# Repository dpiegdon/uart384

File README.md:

<!-- vim: tw=72 fo+=a
-->

UART384 - FPGA devboard & USB-stick
===================================

<div>

</div>

<div>

</div>

This is a mini-devboard for the Lattice iCE40LP384, the *BEST* 🔍 FPGA
ever!

Features:
- USB-stick form-factor
- USB is connected to Silabs CP2102 USB-to-UART bridge
- Tiny Lattice iCE40LP384 with connections:
  - 384 LUTs/FFs
  - UART
  - 2 LEDs
  - 1 push-button
  - 8 GPIOs on pinheader
  - 32MHz oscillator
- small flash for bitstream
- TC2050 connector (bottom side) for programming the flash

NOTE: device is not programmable via USB

Gateware
========

"Why?", you ask?

Mostly for fun and training; there are a few gateware options available in this repository:

Entropy generator
-----------------

`gateware/entropy_generator.v`

High quality entropy source using metastability from ringoscillators fed
into the spongent hash algorithm. 

This is one of the original reasons this board was created for: I wanted
a USB stick that generates cryptographically sound entropy that can be
used to enhance system entropy on linux.

`gateware/tools/seedrng.py` can be used to receive the entropy and
inject it directly into the kernel entropy pool.

SPI and GPIO over UART tunnel
-----------------------------

`gateware/relay_spi.v`

This variant allows complex muxing of SPI lines from an SPI master core
to all GPIO1..8 pins, as well as the internal program flash. All these
pins can also be muxed as GPIO input or output and controlled/sampled.
All that via a simple UART protocol.

This gives full control of inputs and outputs, as well as efficient SPI
communication via SPI core, in any configuration. The SPI core is used
for SPI transfer by pulling RTS down, then CS is automatically pulled
down and data is seemlessly interchanged between SPI and UART.

This e.g. allows reprogramming the internal flash, or external SPI
devices, including Lattice iCE40 FPGAs if GPIOs are used to trigger
their CRESET. Since CDONE can also be sampled, this also allows
programming any iCE40 FPGA in slave mode, fully replacing any other
needed programming board to flash/program a Lattice iCE40 FPGA. Note
that the FPGA is pretty much full, no further features will be added to
this gateware.

See `gateware/tools/spi_device.py` for general SPI command abstraction,
and `gateware/tools/flashtool.py` and `gateware/tools/spi_device.py` as
an example client to work with the onboard (or any other) serial flash.

Ring oscillator entropy generator
---------------------------------

`gateware/ring_noise.v`

Low quality entropy generator using metastability from ringoscillators
fed into a linear feedback shift register.

UART pass-through
-----------------

`gateware/uart_passthrough.v`

A simple example that only passes UART signals along to the GPIO header
and shows changes on RX/TX lines on the LEDs (with some timeout).

Variable delay ring oscillator
------------------------------

`gateware/variable_ringoscillator.v`

Experiments with a ringoscillator with a reconfigurable delay-line.
Delay can be changed at runtime via UART.

License
=======

The hardware (Schematic, PCB) is licensed under CERN-OHL-W v2.
See `cern_ohl_w_v2.txt`.

The software is licensed under LGPL v2.0, unless specified otherwise
in a subrepository. See `LGPLv2.0.txt`.

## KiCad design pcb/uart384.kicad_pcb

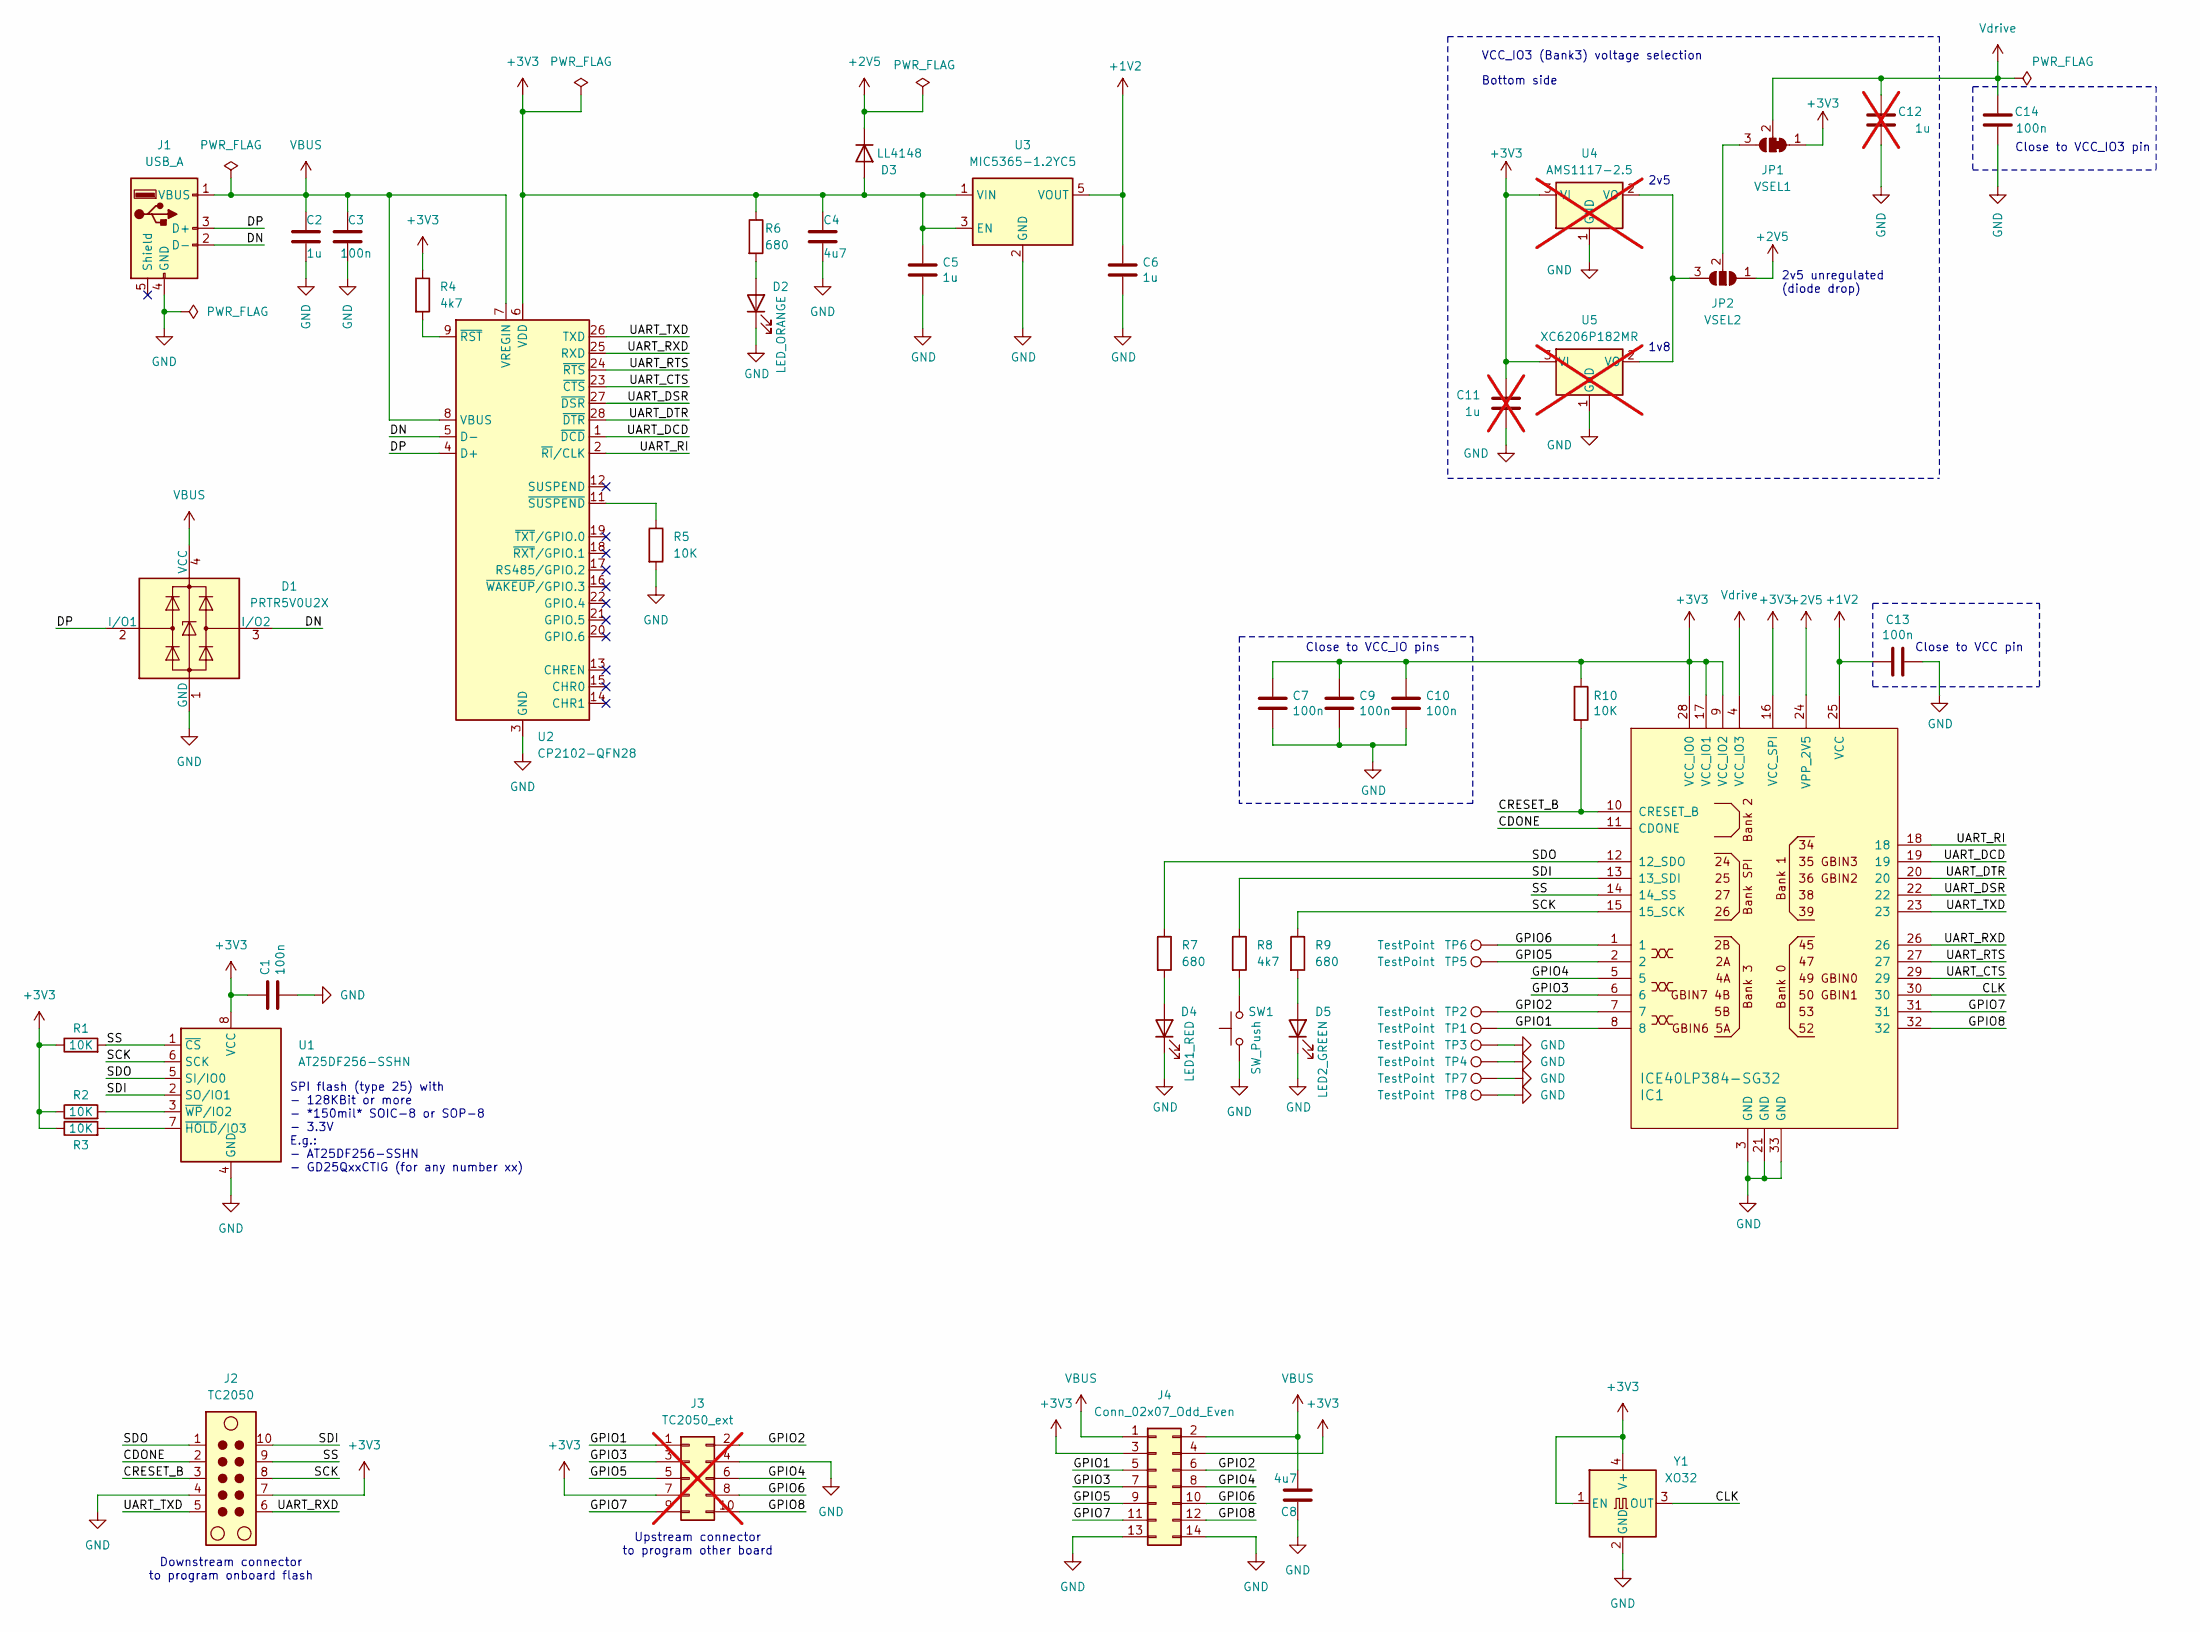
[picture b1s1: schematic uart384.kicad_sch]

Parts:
C1, C3, C7, C9, C10, C13, C14: 100n; C_0603_1608Metric
C2, C5, C6: 1u; C_0603_1608Metric
C4, C8: 4u7; C_0603_1608Metric
C11, C12: 1u; C_0603_1608Metric; not fitted
D1: PRTR5V0U2X; SOT-143
D2: LED_ORANGE; LED_0603_1608Metric
D3: LL4148; D_MiniMELF
D4: LED1_RED; LED_0603_1608Metric
D5: LED2_GREEN; LED_0603_1608Metric
IC1: ICE40LP384-SG32; QFN-32-1EP_5x5mm_P0.5mm_EP3.6x3.6mm
J1: USB_A; CONN-USB-A-PCB-TRACES
J2: TC2050; Tag-Connect_TC2050-IDC-NL_2x05_P1.27mm_Vertical
J3: TC2050_ext; PinHeader_2x05_P2.54mm_Vertical_SMD; not fitted
J4: Conn_02x07_Odd_Even; PinHeader_2x07_P2.54mm_Vertical_SMD
JP1: VSEL1; SolderJumper-3_P1.3mm_Bridged2Bar12_RoundedPad1.0x1.5mm
JP2: VSEL2; SolderJumper-3_P1.3mm_Open_RoundedPad1.0x1.5mm
R1, R2, R3, R5, R10: 10K; R_0603_1608Metric
R4, R8: 4k7; R_0603_1608Metric
R6, R7, R9: 680; R_0603_1608Metric
SW1: SW_Push; TS-1224W_Side_Button_2x4x3.3mm_3.5mm_3.8mm_SMD_Aliexpress
TP1, TP2, TP3, TP4, TP5, TP6, TP7, TP8: TestPoint; TestPoint_Pad_1.0x1.0mm
U1: AT25DF256-SSHN; SOIC-8_3.9x4.9mm_P1.27mm
U2: CP2102-QFN28; QFN-28-1EP_5x5mm_P0.5mm_EP3.35x3.35mm
U3: MIC5365-1.2YC5; SOT-353_SC-70-5
U4: AMS1117-2.5; SOT-223-3_TabPin2; not fitted
U5: XC6206P182MR; SOT-23-3; not fitted
Y1: XO32; Oscillator_SMD_EuroQuartz_XO32-4Pin_3.2x2.5mm

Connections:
+1V2: C6.1, C13.2, IC1.25 (VCC), U3.5 (VOUT)
+2V5: D3.1 (K), IC1.24 (VPP_2V5), JP2.1 (A)
+3V3: C1.1, C4.1, C5.1, C7.1, C9.1, C10.1, C11.2, D3.2 (A), IC1.9 (VCC_IO2), IC1.16 (VCC_SPI), IC1.17 (VCC_IO1), IC1.28 (VCC_IO0), J2.7, J3.7, J4.3, J4.4, JP1.1 (A), R1.1, R2.1, R3.1, R4.1, R6.1, R10.1, U1.8 (VCC), U2.6 (VDD), U3.1 (VIN), U3.3 (EN), U4.3 (VI), U5.3 (VI), Y1.1 (EN), Y1.4 (V+)
/CDONE: IC1.11 (CDONE), J2.2
/CLK: IC1.30, Y1.3 (OUT)
/CRESET_B: IC1.10 (CRESET_B), J2.3, R10.2
/DN: D1.3 (I/O2), J1.2 (D-), U2.5 (D-)
/DP: D1.2 (I/O1), J1.3 (D+), U2.4 (D+)
/GPIO1: IC1.8, J3.1, J4.5, TP1.1
/GPIO2: IC1.7, J3.2, J4.6, TP2.1
/GPIO3: IC1.6, J3.3, J4.7
/GPIO4: IC1.5, J3.6, J4.8
/GPIO5: IC1.2, J3.5, J4.9, TP5.1
/GPIO6: IC1.1, J3.8, J4.10, TP6.1
/GPIO7: IC1.31, J3.9, J4.11
/GPIO8: IC1.32, J3.10, J4.12
/SCK: IC1.15 (15_SCK), J2.8, R9.1, U1.6 (SCK)
/SDI: IC1.13 (13_SDI), J2.10, R8.1, U1.2 (SO/IO1)
/SDO: IC1.12 (12_SDO), J2.1, R7.1, U1.5 (SI/IO0)
/SS: IC1.14 (14_SS), J2.9, R1.2, U1.1 (~CS)
/UART_CTS: IC1.29, U2.23 (~CTS)
/UART_DCD: IC1.19, U2.1 (~DCD)
/UART_DSR: IC1.22, U2.27 (~DSR)
/UART_DTR: IC1.20, U2.28 (~DTR)
/UART_RI: IC1.18, U2.2 (~RI/CLK)
/UART_RTS: IC1.27, U2.24 (~RTS)
/UART_RXD: IC1.26, J2.6, U2.25 (RXD)
/UART_TXD: IC1.23, J2.5, U2.26 (TXD)
GND: C1.2, C2.2, C3.2, C4.2, C5.2, C6.2, C7.2, C8.1, C9.2, C10.2, C11.1, C12.1, C13.1, C14.1, D1.1 (GND), D2.1 (K), D4.1 (K), D5.1 (K), IC1.3 (GND), IC1.21 (GND), IC1.33 (GND), J1.4 (GND), J2.4, J3.4, J4.13, J4.14, R5.2, SW1.1, TP3.1, TP4.1, TP7.1, TP8.1, U1.4 (GND), U2.3 (GND), U2.29 (GND), U3.2 (GND), U4.1 (GND), U5.1 (GND), Y1.2 (GND)
unnamed: D2.2 (A), R6.2
unnamed: D4.2 (A), R7.2
unnamed: D5.2 (A), R9.2
unnamed: JP1.3 (B), JP2.2 (C)
unnamed: JP2.3 (B), U4.2 (VO), U5.2 (VO)
unnamed: R8.2, SW1.2
unnamed: R3.2, U1.7 (~HOLD/IO3)
unnamed: R2.2, U1.3 (~WP/IO2)
unnamed: R4.2, U2.9 (~RST)
unnamed: R5.1, U2.11 (~SUSPEND)
VBUS: C2.1, C3.1, C8.2, D1.4 (VCC), J1.1 (VBUS), J4.1, J4.2, U2.7 (VREGIN), U2.8 (VBUS)
Vdrive: C12.2, C14.2, IC1.4 (VCC_IO3), JP1.2 (C)

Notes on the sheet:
Upstream connector to program other board
VCC_IO3 (Bank3) voltage selection
2v5 unregulated (diode drop)
SPI flash (type 25) with - 128KBit or more - *150mil* SOIC-8 or SOP-8 - 3.3V E.g.: - AT25DF256-SSHN - GD25QxxCTIG (for any number xx)
Bottom side
2v5
1v8
Close to VCC pin
Downstream connector to program onboard flash
Close to VCC_IO pins
Close to VCC_IO3 pin

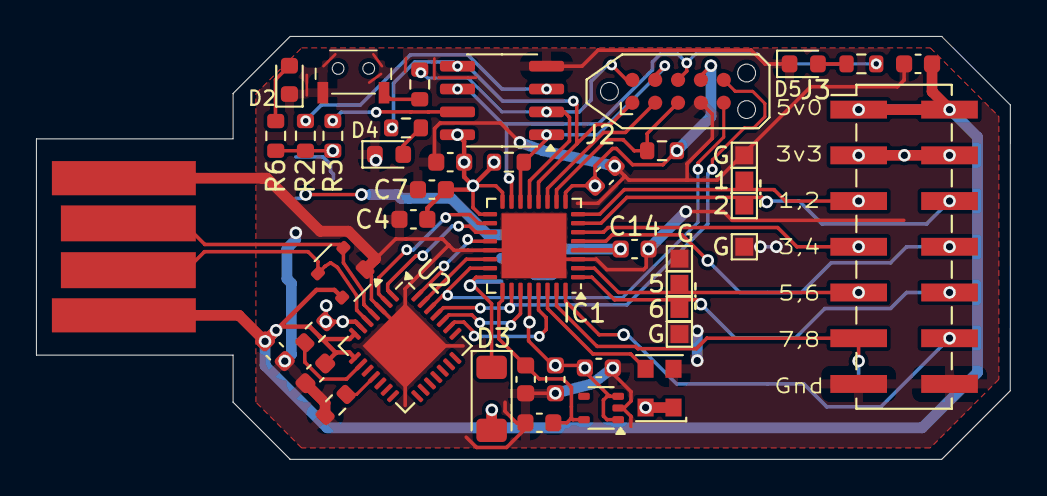
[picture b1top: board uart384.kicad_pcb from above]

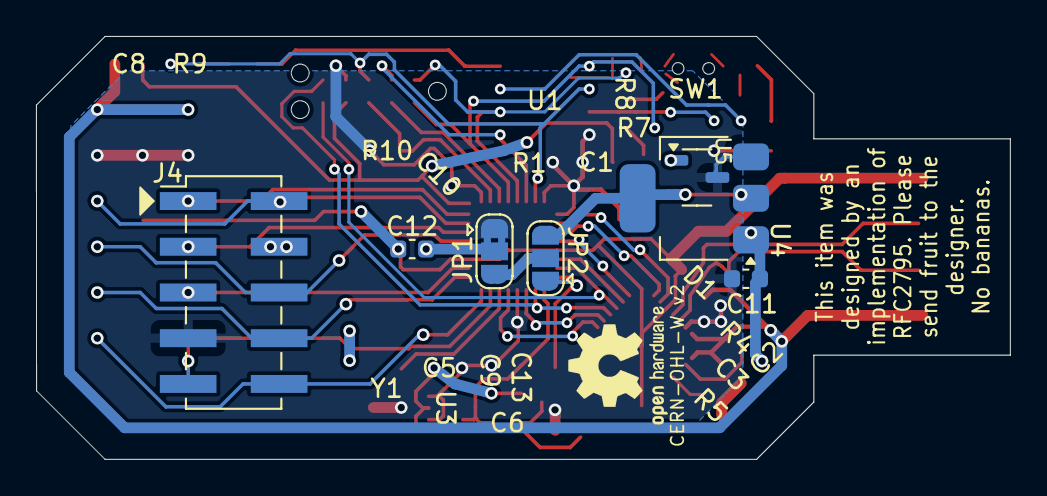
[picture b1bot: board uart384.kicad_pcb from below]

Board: 2 copper layers, 54.1 x 23.5 mm, 51 parts (7 on the bottom side), 41 nets.

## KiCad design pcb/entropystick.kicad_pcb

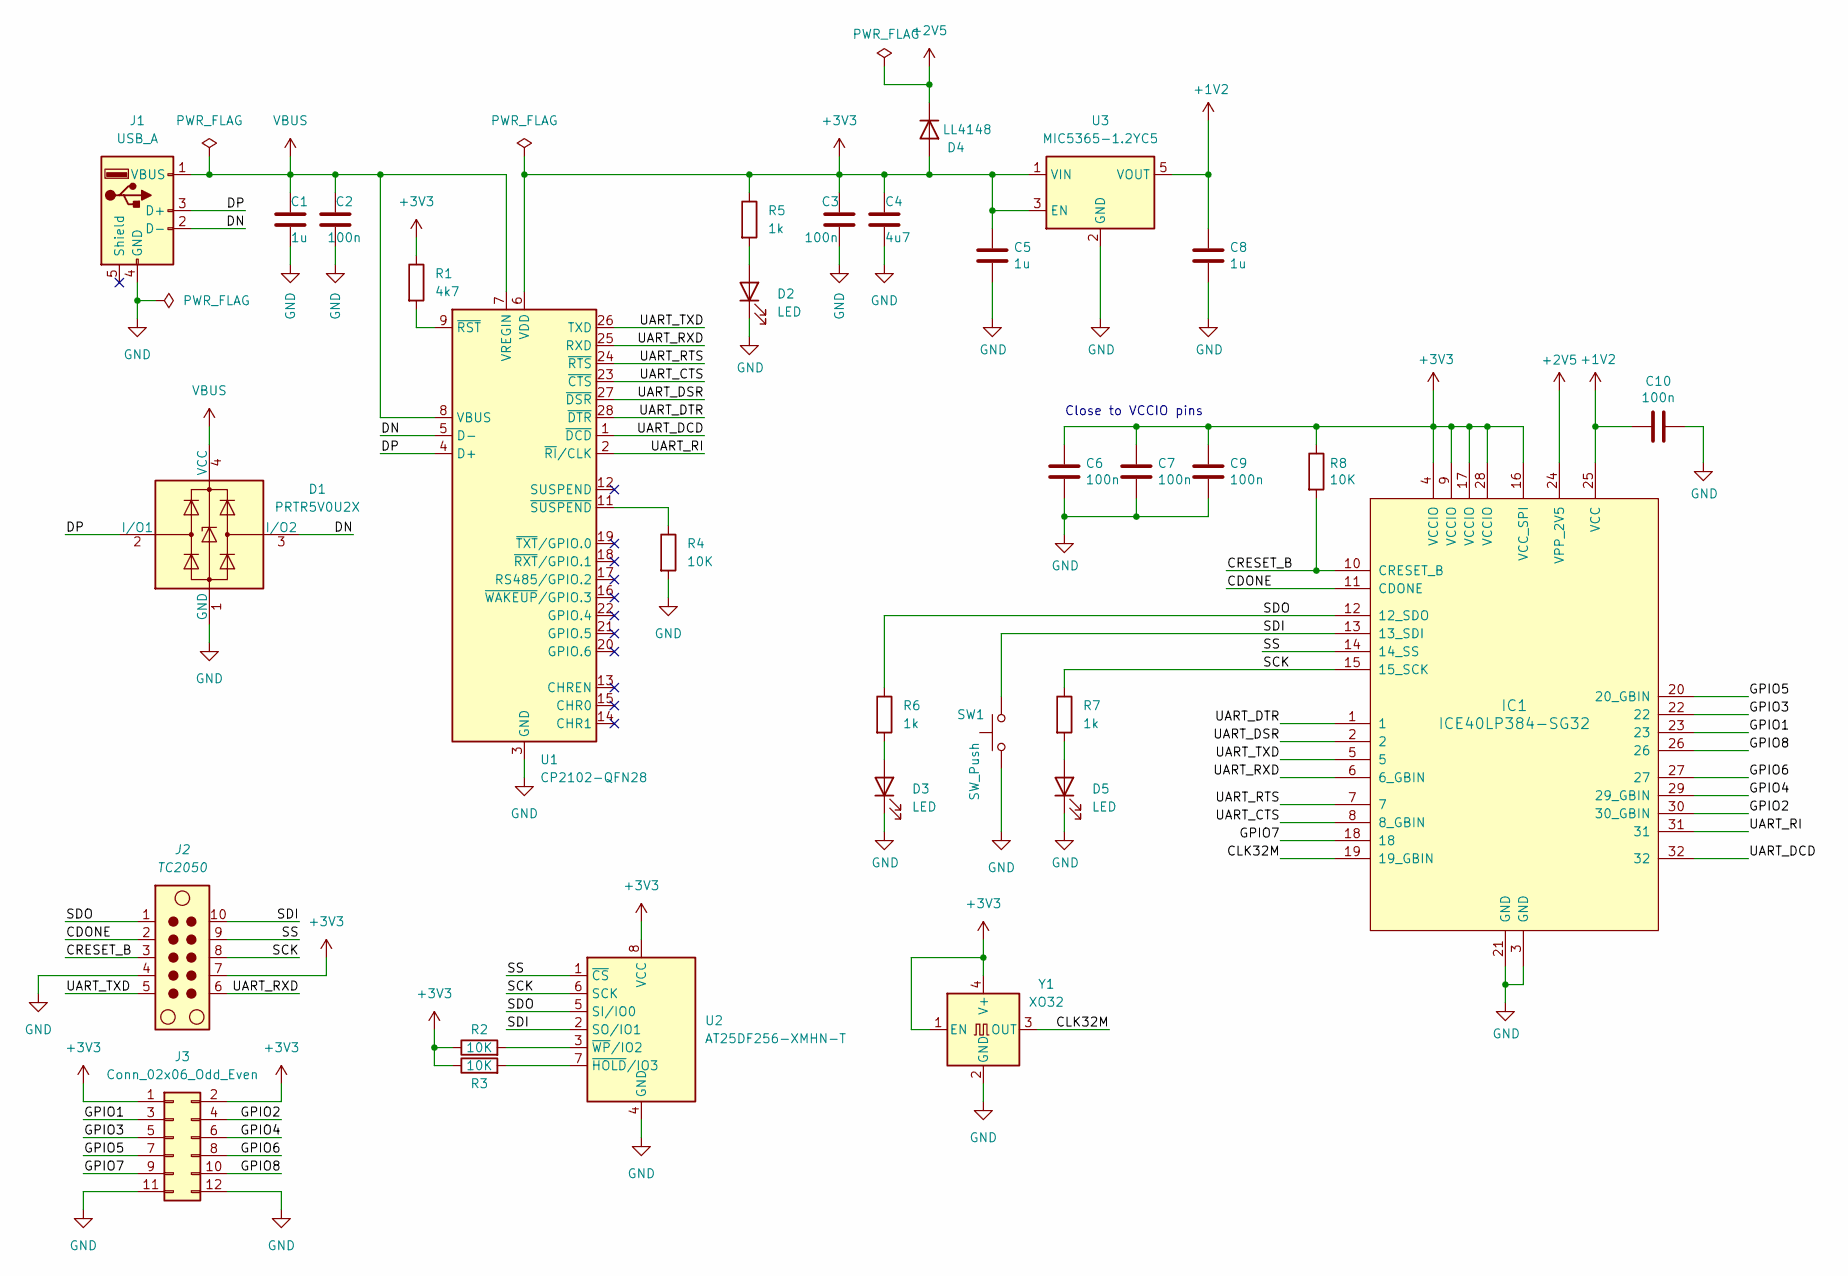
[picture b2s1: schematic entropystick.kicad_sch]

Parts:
C1, C5, C8: 1u; C_0603_1608Metric
C2, C3, C6, C7, C9, C10: 100n; C_0603_1608Metric
C4: 4u7; C_0603_1608Metric
D1: PRTR5V0U2X; SOT-143
D2, D3, D5: LED; LED_0603_1608Metric
D4: LL4148; D_MiniMELF
IC1: ICE40LP384-SG32; QFN-32-1EP_5x5mm_P0.5mm_EP3.6x3.6mm
J1: USB_A; CONN-USB-A-PCB-TRACES
J2: TC2050; Tag-Connect_TC2050-IDC-NL_2x05_P1.27mm_Vertical
J3: Conn_02x06_Odd_Even; PinHeader_2x06_P2.54mm_Vertical
R1: 4k7; R_0603_1608Metric
R2, R3, R4, R8: 10K; R_0603_1608Metric
R5, R6, R7: 1k; R_0603_1608Metric
SW1: SW_Push; TS-1224W_Side_Button_2x4x3.3mm_3.5mm_3.8mm_SMD_Aliexpress
U1: CP2102-QFN28; QFN-28-1EP_5x5mm_P0.5mm_EP3.35x3.35mm
U2: AT25DF256-XMHN-T; SOIC-8_3.9x4.9mm_P1.27mm
U3: MIC5365-1.2YC5; SOT-353_SC-70-5
Y1: XO32; Oscillator_SMD_EuroQuartz_XO32-4Pin_3.2x2.5mm

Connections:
+1V2: C8.1, C10.2, IC1.25 (VCC), U3.5 (VOUT)
+2V5: D4.1 (K), IC1.24 (VPP_2V5)
+3V3: C3.1, C4.1, C5.1, C6.1, C7.1, C9.1, D4.2 (A), IC1.4 (VCCIO), IC1.9 (VCCIO), IC1.16 (VCC_SPI), IC1.17 (VCCIO), IC1.28 (VCCIO), J2.7, J3.1, J3.2, R1.1, R2.1, R3.1, R5.1, R8.1, U1.6 (VDD), U2.8 (VCC), U3.1 (VIN), U3.3 (EN), Y1.1 (EN), Y1.4 (V+)
/CDONE: IC1.11 (CDONE), J2.2
/CLK32M: IC1.19 (19_GBIN), Y1.3 (OUT)
/CRESET_B: IC1.10 (CRESET_B), J2.3, R8.2
/DN: D1.3 (I/O2), J1.2 (D-), U1.5 (D-)
/DP: D1.2 (I/O1), J1.3 (D+), U1.4 (D+)
/GPIO1: IC1.23, J3.3
/GPIO2: IC1.30 (30_GBIN), J3.4
/GPIO3: IC1.22, J3.5
/GPIO4: IC1.29 (29_GBIN), J3.6
/GPIO5: IC1.20 (20_GBIN), J3.7
/GPIO6: IC1.27, J3.8
/GPIO7: IC1.18, J3.9
/GPIO8: IC1.26, J3.10
/SCK: IC1.15 (15_SCK), J2.8, R7.1, U2.6 (SCK)
/SDI: IC1.13 (13_SDI), J2.10, SW1.2, U2.2 (SO/IO1)
/SDO: IC1.12 (12_SDO), J2.1, R6.1, U2.5 (SI/IO0)
/SS: IC1.14 (14_SS), J2.9, U2.1 (~CS)
/UART_CTS: IC1.8 (8_GBIN), U1.23 (~CTS)
/UART_DCD: IC1.32, U1.1 (~DCD)
/UART_DSR: IC1.2, U1.27 (~DSR)
/UART_DTR: IC1.1, U1.28 (~DTR)
/UART_RI: IC1.31, U1.2 (~RI/CLK)
/UART_RTS: IC1.7, U1.24 (~RTS)
/UART_RXD: IC1.6 (6_GBIN), J2.6, U1.25 (RXD)
/UART_TXD: IC1.5, J2.5, U1.26 (TXD)
GND: C1.2, C2.2, C3.2, C4.2, C5.2, C6.2, C7.2, C8.2, C9.2, C10.1, D1.1 (GND), D2.1 (K), D3.1 (K), D5.1 (K), IC1.3 (GND), IC1.21 (GND), J1.4 (GND), J2.4, J3.11, J3.12, R4.2, SW1.1, U1.3 (GND), U1.29 (GND), U2.4 (GND), U3.2 (GND), Y1.2 (GND)
unnamed: D2.2 (A), R5.2
unnamed: D3.2 (A), R6.2
unnamed: D5.2 (A), R7.2
unnamed: R1.2, U1.9 (~RST)
unnamed: R4.1, U1.11 (~SUSPEND)
unnamed: R3.2, U2.7 (~HOLD/IO3)
unnamed: R2.2, U2.3 (~WP/IO2)
VBUS: C1.1, C2.1, D1.4 (VCC), J1.1 (VBUS), U1.7 (VREGIN), U1.8 (VBUS)

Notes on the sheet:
Close to VCCIO pins

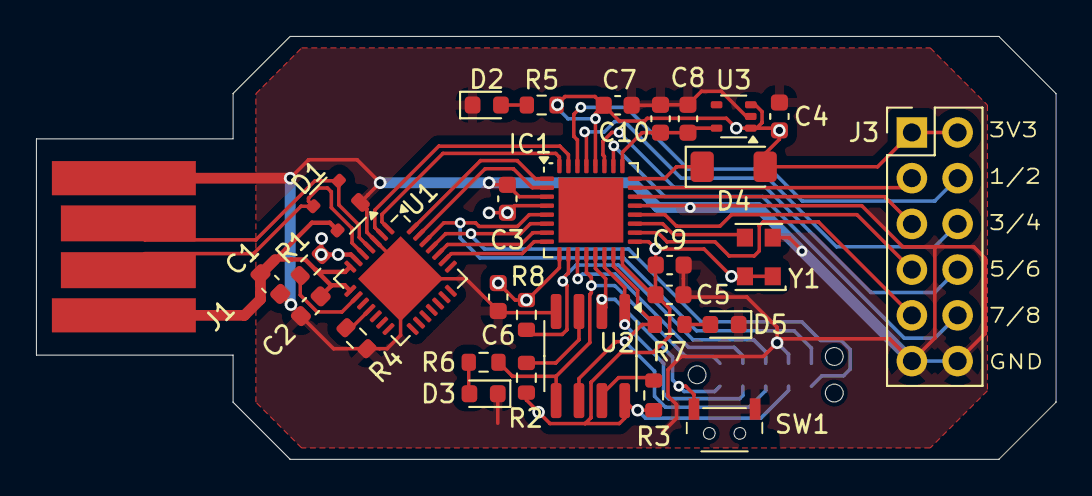
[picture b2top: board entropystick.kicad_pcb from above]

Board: 2 copper layers, 56.6 x 23.5 mm, 32 parts (1 on the bottom side), 37 nets.

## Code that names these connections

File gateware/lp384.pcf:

set_io --warn-no-port uart_dtr 1
set_io --warn-no-port uart_dsr 2
set_io --warn-no-port uart_txd 5
set_io --warn-no-port uart_rxd 6
set_io --warn-no-port uart_rts 7
set_io --warn-no-port uart_cts 8
set_io --warn-no-port uart_ri  31
set_io --warn-no-port uart_dcd 32

set_io --warn-no-port clk32m   19

set_io --warn-no-port gpio1    23
set_io --warn-no-port gpio2    30
set_io --warn-no-port gpio3    22
set_io --warn-no-port gpio4    29
set_io --warn-no-port gpio5    20
set_io --warn-no-port gpio6    27
set_io --warn-no-port gpio7    18
set_io --warn-no-port gpio8    26

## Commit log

2025-08-24 initial draft concept
2025-08-25 improve pin assignments, place&route
2025-08-26 improve PCB
2025-08-26 add switch, LED; verify USB connector dimensions
2025-08-26 rename to uart384, since hardware is generic
2025-08-26 update gateware PCF; add notes, README, documentation
2025-08-26 setup 3d models, PCB color; create rendering; improve docs
2025-08-26 release PCB v1.0: setup production files, docs
2025-08-27 add 3d models of PCB v1.0
2025-08-28 use improved LP384 symbol (no functional changes)
2025-08-28 add uart-passthrough example, improve Makefile and docs
2025-08-29 gateware to test variable ring oscillator, update needed buildingblocks
2025-08-29 clocktest: add uart feedback on which tap is used
2025-08-29 documentation, naming
2025-09-11 add notes on 3d workflow (FreeCAD + Blender)
2025-09-11 expose SPI port to flash, update verilog-buildingblocks.
2025-09-11 PCBv1 Errata: Mismatch between SPI flash footprint and selected part#.
    Part now must be SOIC-8 150mil / SOP-8 150mil.
    Updated part#s in schematic / PCB.
2025-09-16 use improved hashing for entropy generator
2025-09-16 entropy-generator: expose some internal state via LED and GPIO8
2025-09-16 synthesis: run synth_ice40 with `-abc2` to enable optimization at abc stage.
    Enabled parameters are now:
    -dff run 'abc'/'abc9' with -dff option
    -abc2 run two passes of 'abc' for slightly improved logic density
    Adding -abc2 reduces size by about 12 LUTs (328 -> 316).
2025-09-16 improve Makefile to create all graphs.
2025-09-16 makefile cleanup
2025-09-16 makefile: provide rules to use and test random data from entropy generator
2025-09-16 use `clk` instead of `clk32m`.
2025-09-16 use double-time sbox in hashing to improve speed
2025-09-17 use improved modules
2025-09-17 docs
2025-09-18 gateware: inverse LEDs for uart passthrough.
2025-09-18 PCBv1 Errata: SPI SS pullup missing
2025-09-19 name LEDs with used colors. use LEDs for more things.
2025-09-19 fix variable oscillator test
2025-09-20 PCB: add 5V to pinheader, move switch, LED, some resistors, improve routing
2025-09-20 python script to pass entropy to kernel
2025-09-25 implement relay of SPI commands via UART, python script to talk to program-flash
2025-09-25 cleanup
2025-09-25 python tooling to work with SPI flash
2025-09-26 python spi bridge: add security-registers access
2025-09-26 python spi bridge: rebrand and add verification process
2025-09-27 update documentation, latest VBBs
2025-09-27 PCB: add additional header for upstream TC2050, re-route PCB.
    Adding J4 for the "other" side of a TC2050 cable allows programming a
    UART384 with another UART384, once a gateware is written that also can
    control CDONE and CRESET lines. This enables full bootstrapping of a
    UART384 with a UART384 :-D
2025-09-29 PCB: add LP384 GND center pad from upstream symbol, improve schematic and routing
2025-09-29 add CP210x program script and `blink` gateware to test LEDs and GPIOs
2025-09-29 PCB: major hardware revision 2.0~DEV: restructure FPGA pinout, fully reroute.
    - re-map iCE40LP384 pins for GPIO 1-8, UART, CLK to optimize usability
    and allow experiments with LVDS pairs.
    - allow voltage selection for LVDS pins (bank 3) between 3v3 (default)
    and 2v5 (untested, only via diode drop!).
    - make programming pad TC2050 fully available, take care not to place
    components on other side of it.
2025-09-30 PCB: add voltage regulator choices for VCC_IO3, selectable via jumper, DNP
2025-10-02 plaster everything with licenses and copyright notices.
2025-10-03 pick correct PCF: for now v1
2025-10-03 entropy_generator: use double noise source
2025-10-04 optimize the shit out of the PCB because I'm bored.
2025-10-09 PCB: add in-line resistor to switch SW1 to avoid possible shorts.
2025-10-09 gateware: improve relay_spi to allow complex muxing of SPI and configurable GPIO pins
2025-10-11 gateware: relay_spi: reduce and improve available mux functions
2025-10-11 gateware: relay_spi: handle reads always on address-byte
2025-10-11 gateware: relay_spi: allow read-back of mux registers before writing them
2025-10-11 gateware: relay_spi: adapt python script so that it mostly works
2025-10-12 gateware: relay_spi: let python-scripts support programming external flash via TC2050
2025-10-13 gateware: relay_spi: extend features
2025-10-13 add test-pads for easy access to differential pair GPIO1/GPIO2
2025-10-14 PCB: add test-pads for easy access to differential pair GPIO5/GPIO6
2025-10-17 gateware: use improved SPI master from buildingblocks
2025-10-17 docs on spi_relay gateware
2025-10-17 gateware: fix syntax issues for userspace helper
2025-10-18 release PCB v2.0: production files, schematic
2025-10-30 gateware: fix bit-count mismatches
2025-11-07 switch gateware to PCB v2.0
2025-11-07 v2 PCB renderings
2025-11-08 relay_spi: juggle until all important registers can be read back
2025-11-08 python tools: use improved readback register interface, code cleanup
2025-11-08 adopt `black` python formatting rules
    black --line-length 90 --skip-string-normalization
2025-11-09 improve docs
2025-11-09 use logger for debugging/messages
2025-11-25 use latest verilog buildingblocks
2025-11-27 optimize/equalize makefile
2025-11-28 add html BOM for v2.0 PCB
2025-11-29 gateware: relay_spi: fix python-tool to work with v2.0 access to external flash
2025-11-29 delint
2025-12-07 adapt script for setting serial numbers
2025-12-16 photos v2.0
2025-12-22 rework utilization method to prefer `include to use bits of this module.
2025-12-22 fix graph generation
2025-12-22 normalize makefile
2025-12-22 unfold all modules into one-module-per-file
2026-03-29 latest buildingblocks

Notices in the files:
pcb/uart384.kicad_pcb:
(c) 2025 David R. Piegdon
